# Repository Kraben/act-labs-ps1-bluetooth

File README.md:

# ACT Labs REX PS1 Replacement PCB

> Placa de repuesto open-source para el **ACT Labs REX Arcade Stick de PS1**.

```text
Status: Hardware V2 / KiCad actualizado
Firmware publico: PS1 Digital v1.1 OK
Firmware de apoyo: Hybrid AUTO PS1 / PS2 / BLE
BLE: operativo
Fabricacion: Gerbers pendientes de actualizar
Edicion: KiCad completo actualizado
```

## Project Dashboard

| Area | Estado | Alcance |
|---|---|---|
| Hardware | V2 / KiCad actualizado | Publico |
| Firmware PS1 | PS1 Digital v1.1 OK | Publico |
| Firmware binary | [`ActLabs_PS1_Digital_v1.1_OK.bin`](firmware/releases/PS1_Digital/v1.1/ActLabs_PS1_Digital_v1.1_OK.bin) | Publico |
| BLE HID | Operativo | Publico |
| AutoFire | Documentado | Publico |
| KiCad editable | Actualizado en `hardware/kicad/ACT_Labs_REX/` | Publico |
| Gerbers fabricacion | Pendientes de regenerar desde la revision KiCad actual | Publico |
| PS2 / DualShock | Listo en firmware Hybrid AUTO | Build de apoyo / donativos |
| PS1/PS2/BLE Hybrid | Listo en firmware Hybrid AUTO | Build de apoyo / donativos |

## Quick Links

| Recurso | Link |
|---|---|
| Sitio web | https://kraben.github.io/act-labs-ps1-bluetooth/ |
| Descargar firmware PS1 v1.1 | [`ActLabs_PS1_Digital_v1.1_OK.bin`](firmware/releases/PS1_Digital/v1.1/ActLabs_PS1_Digital_v1.1_OK.bin) |
| Firmware notes | [`docs/firmware.md`](docs/firmware.md) |
| Firmware Hybrid AUTO | [`docs/supporter-build.md`](docs/supporter-build.md) |
| Interfaz PS1 | [`docs/interfaces/ps1.md`](docs/interfaces/ps1.md) |
| Mapeo GPIO | [`docs/mapeo-gpio.md`](docs/mapeo-gpio.md) |
| Conectores | [`docs/conectores.md`](docs/conectores.md) |
| AutoFire | [`docs/autofire.md`](docs/autofire.md) |
| BOM | [`docs/bom.md`](docs/bom.md) |
| Fabricacion | [`docs/fabricacion.md`](docs/fabricacion.md) |
| KiCad editable | [`hardware/kicad/ACT_Labs_REX/`](hardware/kicad/ACT_Labs_REX/) |
| Gerbers | [`hardware/fabrication/gerbers/ACT_Labs_REX/`](hardware/fabrication/gerbers/ACT_Labs_REX/) |

## Resumen

El objetivo de este repositorio es conservar y documentar una alternativa de reemplazo para el control ACT Labs REX, ya que la pieza original ya no se fabrica ni se consigue facilmente.

El sistema usa un ESP32 DevKit V1 como controlador principal para reemplazar la electronica del ACT Labs REX Arcade Stick de PS1.

## Firmware publico PS1

La version publica actual del firmware es:

```text
ActLabs_PS1_Digital_v1.1_OK.bin
```

| Campo | Valor |
|---|---|
| Version | PS1 Digital v1.1 |
| Estado | OK |
| Target | ACT Labs REX PS1 Replacement PCB |
| Hardware | V2 / KiCad actualizado |
| Ruta | [`firmware/releases/PS1_Digital/v1.1/`](firmware/releases/PS1_Digital/v1.1/) |
| Archivo | [`ActLabs_PS1_Digital_v1.1_OK.bin`](firmware/releases/PS1_Digital/v1.1/ActLabs_PS1_Digital_v1.1_OK.bin) |
| SHA256 | `0a8994050381326bf345bf8123c105abefadabf30187247be9129a8c7f34b15c` |
| MD5 | `f61375d0dea1b9e42a6903105f5fba79` |

## Firmware Hybrid AUTO de apoyo

El firmware Hybrid AUTO es una build avanzada para ESP32 pensada como opcion de apoyo/donativos al proyecto.

| Funcion | Estado |
|---|---|
| PS1 cableado | Listo |
| PS2 / DualShock | Listo |
| Bluetooth BLE HID | Listo |
| Deteccion automatica PS1 / PS2 / BLE | Listo |

La documentacion publica se mantiene en [`docs/supporter-build.md`](docs/supporter-build.md). El codigo fuente completo del firmware Hybrid AUTO no se publica en este repositorio publico.

## Modos documentados

| Modo | Descripcion | Estado |
|---|---|---|
| PS1 cableado | ESP32 emula un control digital PS1 usando DATA, CMD, ATT, CLK y ACK. | Publico |
| Bluetooth HID | ESP32 funciona como gamepad BLE cuando se usa con bateria. | Publico |
| AutoFire | Placa secundaria con switches SPDT para activar turbo por boton. | Publico |
| Firmware Hybrid AUTO | PS1 / PS2 / BLE con deteccion automatica. | Build de apoyo / donativos |

## Estructura limpia

```text
.
├── docs/
│   ├── firmware.md
│   ├── supporter-build.md
│   ├── mapeo-gpio.md
│   ├── conectores.md
│   ├── autofire.md
│   └── interfaces/ps1.md
├── hardware/
│   ├── fabrication/
│   │   └── gerbers/
│   │       └── ACT_Labs_REX/
│   ├── kicad/
│   │   └── ACT_Labs_REX/
│   ├── pdf/
│   └── images/
├── data/
└── firmware/
    ├── ACT_Labs_Controller/
    └── releases/
        └── PS1_Digital/
            └── v1.1/
```

## Para fabricar vs para editar

| Uso | Carpeta | Contenido |
|---|---|---|
| Editar proyecto | [`hardware/kicad/ACT_Labs_REX/`](hardware/kicad/ACT_Labs_REX/) | Proyecto KiCad completo actualizado |
| Fabricar PCB | [`hardware/fabrication/gerbers/ACT_Labs_REX/`](hardware/fabrication/gerbers/ACT_Labs_REX/) | Gerbers pendientes de regenerar desde la revision KiCad actual |
| Firmware publico | [`firmware/releases/PS1_Digital/v1.1/`](firmware/releases/PS1_Digital/v1.1/) | Binario PS1 Digital v1.1 |
| Revisar PDFs | [`hardware/pdf/`](hardware/pdf/) | Esquematicos y PCB en PDF |
| Revisar datos | [`data/`](data/) | Mapeos, CSV y hojas de apoyo |

## Archivos de fabricacion actuales

> Nota: los Gerbers existentes pueden no corresponder todavia a la revision KiCad mas reciente. Regenerar y validar antes de fabricar.

| Archivo | Proposito |
|---|---|
| `ACT_Labs_REX-F_Cu.gbr` | Cobre superior |
| `ACT_Labs_REX-B_Cu.gbr` | Cobre inferior |
| `ACT_Labs_REX-F_Mask.gbr` | Mascara superior |
| `ACT_Labs_REX-B_Mask.gbr` | Mascara inferior |
| `ACT_Labs_REX-F_Silkscreen.gbr` | Serigrafia superior |
| `ACT_Labs_REX-B_Silkscreen.gbr` | Serigrafia inferior |
| `ACT_Labs_REX-Edge_Cuts.gbr` | Contorno de PCB |
| `ACT_Labs_REX-PTH.drl` | Taladros metalizados |
| `ACT_Labs_REX-NPTH.drl` | Taladros no metalizados |
| `ACT_Labs_REX-job.gbrjob` | Job file de fabricacion |

## Referencias de hardware

| Archivo | Descripcion |
|---|---|
| [`hardware/pdf/ACT_Labs_REX.pdf`](hardware/pdf/ACT_Labs_REX.pdf) | Esquematico principal |
| [`hardware/pdf/ArcLabsPCB.pdf`](hardware/pdf/ArcLabsPCB.pdf) | PCB principal |
| [`hardware/pdf/AutoFire.pdf`](hardware/pdf/AutoFire.pdf) | Esquematico AutoFire |
| [`hardware/pdf/AutoFirePCB.pdf`](hardware/pdf/AutoFirePCB.pdf) | PCB AutoFire |
| [`hardware/fabrication/`](hardware/fabrication/) | BOM/POS de fabricacion |

## Pines principales V2

| Signal | GPIO |
|---|---:|
| DATA | 19 |
| CMD | 23 |
| ATT | 5 |
| CLK | 18 |
| ACK | 4 |
| START | 2 |
| SELECT | 16 |
| AF_MODE | 15 |

## Apoyo / donativos

GitHub Pages puede funcionar como landing page del proyecto y enlazar a una plataforma externa para apoyo/donativos.

Opciones recomendadas:

| Opcion | Uso recomendado |
|---|---|
| GitHub Pages + PayPal/Mercado Pago | Catalogo simple y contacto directo |
| GitHub Pages + Gumroad/Payhip/Ko-fi | Entrega de builds de apoyo, firmware o archivos digitales |
| GitHub Pages + Stripe Payment Links | Botones de pago profesionales sin backend propio |
| GitHub Sponsors | Apoyo/donaciones recurrentes |

El repositorio publico mantiene hardware, documentacion y firmware PS1 disponible. La build Hybrid AUTO se maneja como opcion avanzada de apoyo para sostener el desarrollo.

## Proximos pasos

- [ ] Regenerar Gerbers desde la revision KiCad actual.
- [ ] Validar Gerbers nuevos contra visualizador antes de mandar a fabricar.
- [ ] Validar continuidad START/SELECT contra GND en PCB actualizada.
- [ ] Validar continuidad entre PCB principal, placa AutoFire y conectores JP.
- [ ] Revisar la ruta de alimentacion `BATT_FROM_TP`, TP4056, LD1117-3.3 y diodos SS14.
- [ ] Validar el firmware PS1 actualizado contra hardware fisico.
- [ ] Confirmar pull-ups reales contra la PCB antes de fabricar.
- [ ] Preparar binario, checksums y guia de flasheo para la build Hybrid AUTO de apoyo.

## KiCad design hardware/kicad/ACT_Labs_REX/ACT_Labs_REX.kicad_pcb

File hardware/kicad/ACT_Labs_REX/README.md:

# ACT Labs REX KiCad Sources

Fuentes editables de KiCad para **ACT Labs REX PCB V2.2**.

## Uso

Esta carpeta es para editar el proyecto en KiCad.

Para fabricar usar los Gerbers exportados en:

```text
hardware/fabrication/gerbers/ACT_Labs_REX/
```

## Archivos principales

| Archivo | Proposito |
|---|---|
| ACT_Labs_REX.kicad_pro | Proyecto KiCad |
| ACT_Labs_REX.kicad_sch | Esquematico principal |
| ACT_Labs_REX.kicad_pcb | PCB principal |
| Placa_2.kicad_sch | Esquematico de placa secundaria / AutoFire |

## Reglas

- Mantener aqui solo fuentes editables de KiCad.
- No mezclar Gerbers ni salidas de fabricacion en esta carpeta.
- No subir backups, autosaves ni archivos temporales.
- Exportar salidas de fabricacion hacia `hardware/fabrication/gerbers/ACT_Labs_REX/`.

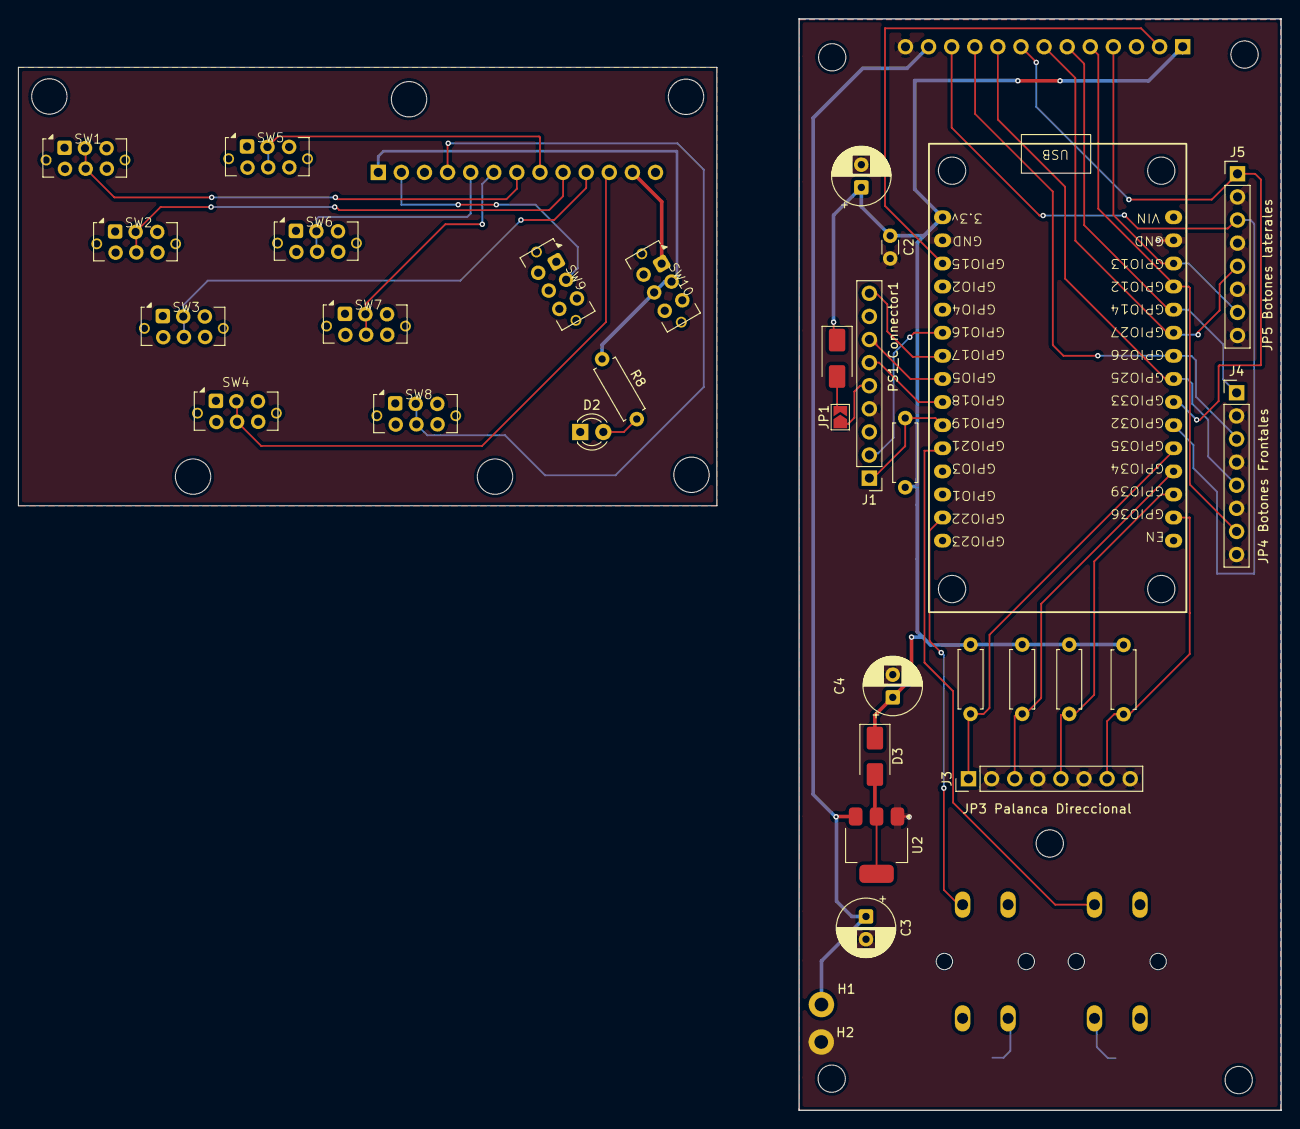
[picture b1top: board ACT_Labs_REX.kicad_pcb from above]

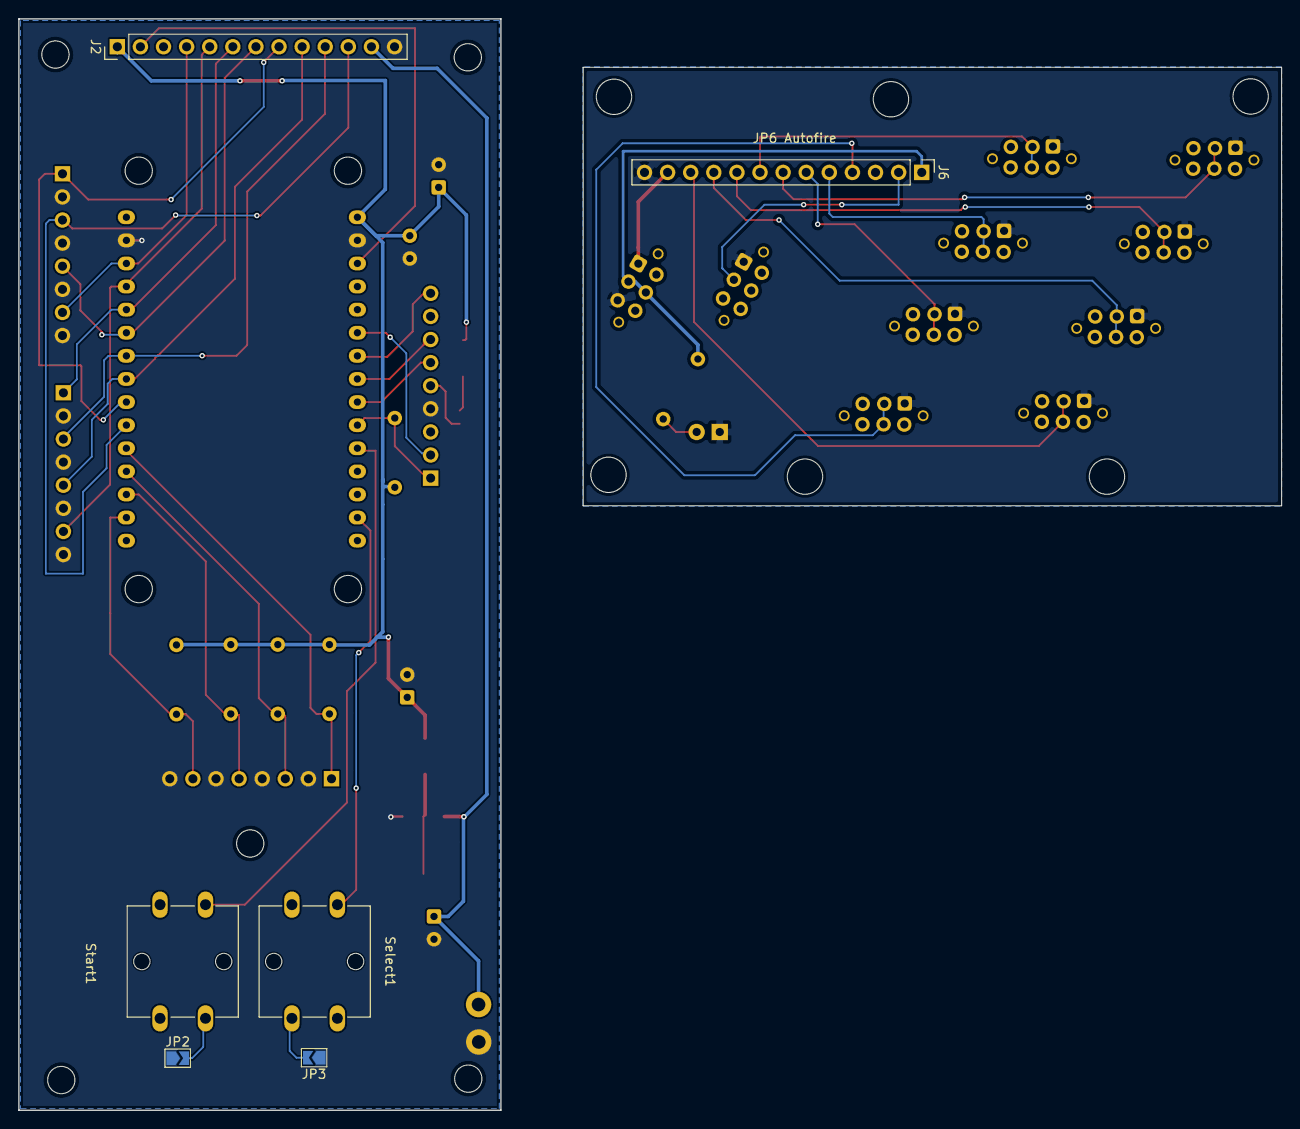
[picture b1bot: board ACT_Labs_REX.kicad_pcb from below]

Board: 2 copper layers, 138.8 x 120.0 mm, 38 parts (6 on the bottom side), 35 nets.

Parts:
C1: 220µF; CP_Radial_D6.3mm_P2.50mm
C2: 100nF; C_Disc_D3.0mm_W1.6mm_P2.50mm
C3, C4: 10µF; CP_Radial_D6.3mm_P2.50mm
D1, D3: SS14; D_SMA
D2: LED; LED_D3.0mm
H1, H2: TP4056; MountingHole_2.5mm_Pad
J1: PS1_Connector1; PinHeader_1x09_P2.54mm_Vertical
J2: JP1 Autofire; PinHeader_1x13_P2.54mm_Vertical
J3: JP3 Palanca Direccional; PinHeader_1x08_P2.54mm_Vertical
J4: JP4 Botones Frontales; PinHeader_1x08_P2.54mm_Vertical
J5: JP5 Botones laterales; PinHeader_1x08_P2.54mm_Vertical
J6: JP6 Autofire; PinHeader_1x13_P2.54mm_Vertical
JP1, JP2, JP3: SolderJumper_2_Open; SolderJumper-2_P1.3mm_Open_TrianglePad1.0x1.5mm
R1, R2, R3, R4, R5: 10kΩ; R_Axial_DIN0207_L6.3mm_D2.5mm_P7.62mm_Horizontal
R8: 220Ω; R_Axial_DIN0207_L6.3mm_D2.5mm_P7.62mm_Horizontal
SW1, SW2, SW3, SW4, SW5, SW6, SW7, SW8, SW9, SW10: SW_SPDT; Untitled_1
Select1: SW_Omron_B3FS; SW_SPST_Omron_B3F-50xx
Start1: SW_Omron_B3FS; SW_SPST_Omron_B3F-50xx
U1: ESP32_30pin
U2: LD1117S33TR_SOT223; SOT-223-3_TabPin2

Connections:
//AF_CIRCULO: J2.10, J4.3, U1.7 (GPIO26)
//AF_CRUZ: J2.9, J4.5, U1.8 (GPIO25)
//AF_CUADRADO: J2.5, J4.7, U1.4 (GPIO12)
//AF_L1: J2.7, J5.5, U1.6 (GPIO27)
//AF_L2: J2.11, J5.3, U1.10 (GPIO32)
//AF_MODE: J2.2, U1.18 (GPIO15)
//AF_R1: J2.8, J5.1, U1.9 (GPIO33)
//AF_R2: J2.4, J5.7, U1.3 (GPIO13)
//AF_TRIANGULO: J2.6, J4.1, U1.5 (GPIO14)
//AutoFire/AF_CIRCULO: J6.10, SW3.2 (B), SW3.5
//AutoFire/AF_CRUZ: J6.9, SW2.2 (B), SW2.5
//AutoFire/AF_CUADRADO: J6.5, SW6.2 (B), SW6.5
//AutoFire/AF_L1: J6.7, SW1.2 (B), SW1.5
//AutoFire/AF_L2: J6.11, SW4.2 (B), SW4.5
//AutoFire/AF_MODE: J6.2, SW9.2 (B)
//AutoFire/AF_R1: J6.8, SW5.2 (B), SW5.5
//AutoFire/AF_R2: J6.4, SW8.2 (B), SW8.5
//AutoFire/AF_TRIANGULO: J6.6, SW7.2 (B), SW7.5
//AutoFire/GND: D2.1 (K), J6.13, SW1.1 (A), SW2.1 (A), SW3.1 (A), SW4.1 (A), SW5.1 (A), SW6.1 (A), SW7.1 (A), SW8.1 (A), SW9.1 (A), SW10.3 (C)
//AutoFire/LED: D2.2 (A), R8.2
//GND: C1.2, C2.2, C3.2, C4.2, H2.1 (1_1), J1.4, J2.13, J3.2, J3.4, J3.6, J3.8, J4.2, J4.4, J4.6, J4.8, J5.2, J5.4, J5.6, J5.8, JP2.1 (A), JP3.1 (A), U1.2 (GND), U1.17 (GND), U2.1 (GND)
//JP3_ABAJO: J3.1, R4.2, U1.11 (GPIO35)
//JP3_ARRIBA: J3.7, R2.2, U1.14 (GPIO36)
//JP3_DERECHA: J3.5, R5.2, U1.13 (GPIO39)
//JP3_IZQUIERDA: J3.3, R3.2, U1.12 (GPIO34)
//PS1_ACK: J1.9, U1.22 (GPIO17)
//PS1_ATT: J1.6, U1.24 (GPIO18)
//PS1_CLK: J1.7, U1.23 (GPIO5)
//PS1_CMD: J1.2, U1.21 (GPIO16)
//PS1_DATA: J1.1, R1.2, U1.25 (GPIO19)
//SELECT: JP3.2 (B), Select1.3, Select1.4, U1.29 (GPIO22)
//START: JP2.2 (B), Start1.1 (1_1), Start1.4, U1.26 (GPIO21)
BATT_FROM_TP: C3.1, H1.1 (1_1), J2.12, J6.12, SW10.1 (A), U2.3 (VI)
PS1_PIN5: D1.2 (A), J1.5, JP1.1 (A), JP1.2 (B)
VCC_3V3: C1.1, C2.1, C4.1, D1.1 (K), D3.1 (K), D3.2 (A), J2.1, J6.1, R1.1, R2.1, R3.1, R4.1, R5.1, R8.1, SW10.2 (B), SW10.5, U1.16 (3.3v), U2.2 (VO)

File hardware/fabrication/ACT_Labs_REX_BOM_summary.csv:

Reference,Value,Quantity
C1,220uF,1
C2,100nF,1
C3,10uF,1
C4,10uF,1
D1,SS14,1
D2,LED,1
D3,SS14,1
J1,PS1_Connector1,1
J2,JP1_Autofire,1
J3,JP3_Palanca_Direccional,1
J4,JP4_Botones_Frontales,1
J5,JP5_Botones_laterales,1
J6,JP6_Autofire,1
R1,10k,1
R2,10k,1
R3,10k,1
R4,10k,1
R5,10k,1
R6,4.7k,1
R7,4.7k,1
R8,220R,1
Select1,SW_Omron_B3FS,1
Start1,SW_Omron_B3FS,1
SW1,SW_SPDT,1
SW2,SW_SPDT,1
SW3,SW_SPDT,1
SW4,SW_SPDT,1
SW5,SW_SPDT,1
SW6,SW_SPDT,1
SW7,SW_SPDT,1
SW8,SW_SPDT,1
SW9,SW_SPDT,1
SW10,SW_SPDT,1
U1,ESP32_30pin,1
U2,LD1117S33TR_SOT223,1

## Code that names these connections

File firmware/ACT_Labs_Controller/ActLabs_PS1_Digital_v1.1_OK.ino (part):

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  - Turbo opcional.

  Pines protocolo:
    DATA = GPIO19  ESP32 -> PS1
    CMD  = GPIO23  PS1 -> ESP32
    ATT  = GPIO5   PS1 -> ESP32
    CLK  = GPIO18  PS1 -> ESP32
    ACK  = GPIO4   ESP32 -> PS1

  Pull-ups recomendados:
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// PINES PS1
// =====================================================

#define PS1_DATA  19
#define PS1_CMD   23
#define PS1_ATT   5
#define PS1_CLK   18
#define PS1_ACK   4

// =====================================================
// BOTONES SEGUN ESQUEMATICO ACTLABS
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
#define PIN_START      21
#define PIN_SELECT     22
#define PIN_AF_MODE    15

// =====================================================
// MAPA PS1 DIGITAL
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volatile uint32_t ps1_att_count = 0;
volatile uint32_t ps1_clk_count = 0;

static const uint32_t DATA_MASK = (1UL << PS1_DATA);
static const uint32_t ACK_MASK  = (1UL << PS1_ACK);

// =====================================================
// LINEAS OPEN-DRAIN POR REGISTRO
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
  pinMode(PIN_START, INPUT_PULLUP);
  pinMode(PIN_SELECT, INPUT_PULLUP);
  pinMode(PIN_AF_MODE, INPUT_PULLUP);

  // Palanca: GPIO34/35/36/39 con resistencias fisicas externas de 10k.
  pinMode(PIN_ARRIBA, INPUT);
  pinMode(PIN_ABAJO, INPUT);
  pinMode(PIN_IZQUIERDA, INPUT);
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// =====================================================

void setupPs1Pins() {
  pinMode(PS1_CMD, INPUT);
  pinMode(PS1_ATT, INPUT_PULLUP);
  pinMode(PS1_CLK, INPUT_PULLUP);

  // DATA y ACK quedan high-Z.
  dataHighZ();
  ackHighZ();

  attachInterrupt(digitalPinToInterrupt(PS1_ATT), attISR, CHANGE);

  // PS1 funcional: RISING.
  attachInterrupt(digitalPinToInterrupt(PS1_CLK), clkISR, RISING);
}

// =====================================================
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
  Serial.println();
  Serial.println("Mapeo:");
  Serial.println("GPIO25 = X / CRUZ");
  Serial.println("GPIO26 = CIRCLE / CIRCULO");
  Serial.println("GPIO12 = SQUARE / CUADRADO");
  Serial.println("GPIO14 = TRIANGLE / TRIANGULO");
  Serial.println("GPIO27 = L1");
  Serial.println("GPIO33 = R1");
  Serial.println("GPIO32 = L2");
  Serial.println("GPIO13 = R2");
  Serial.println("GPIO21 = START");
  Serial.println("GPIO22 = SELECT");
  Serial.println("GPIO34 = UP");
  Serial.println("GPIO36 = DOWN");
  Serial.println("GPIO39 = LEFT");
  Serial.println("GPIO35 = RIGHT");
  Serial.println();

  Serial.println("Esperado:");
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
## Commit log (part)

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2026-05-08 Initial ACT Labs PS1 Bluetooth project
2026-06-24 V2 PCB checkpoint: LD1117, TP4056, D1, DATA ACK pullups
2026-06-24 Update V2 documentation exports, BOM and fabrication files
2026-06-24 Remove duplicate position exports
2026-06-24 Remove legacy schematic PDF and keep V2 as official release
2026-06-24 docs: actualiza arquitectura V2
2026-06-24 docs: actualiza BOM V2
2026-06-24 docs: actualiza conectores V2
2026-06-24 docs: actualiza firmware V2
2026-06-24 docs: actualiza mapeo GPIO V2
2026-06-24 docs: sincroniza README con hardware V2 y archivos de fabricacion
2026-06-24 docs: documenta arquitectura V2 completa
2026-06-24 docs: actualiza BOM desde exportaciones KiCad V2
2026-06-24 docs: amplía mapeo GPIO V2 para firmware
2026-06-24 docs: actualiza conectores V2 con TP4056 y J1-J6
2026-06-24 docs: actualiza firmware con pines V2 y plan PS1
2026-06-24 docs: actualiza resumen de hardware y fabricacion
2026-06-24 docs: agrega guia de fabricacion V2
2026-06-24 docs: agrega registro de revision V2
2026-06-24 docs: agrega inventario de fuentes KiCad V2
2026-06-24 hardware: agrega resumen BOM placa principal V2
2026-06-24 hardware: agrega resumen POS placa principal V2
2026-06-24 hardware: agrega resumen BOM AutoFire V2
2026-06-24 hardware: agrega resumen POS AutoFire V2
2026-06-24 docs: ajusta referencias a archivos de fabricacion cargados
2026-06-24 docs: ajusta hardware README a resumenes de fabricacion
2026-06-24 docs: corrige START y SELECT segun mapeo consolidado
2026-06-24 docs: sincroniza mapeo GPIO con Rev 1.4
2026-06-24 docs: sincroniza firmware con resumen y pines Rev 1.4
2026-06-24 docs: consolida conectores y corrige tabla JP1
2026-06-24 docs: corrige revision V2 con mapeo Rev 1.4
2026-06-24 docs: actualiza inventario de fuentes y hashes Rev 1.4
2026-06-26 docs: agrega arquitectura de interfaces
2026-06-26 docs: agrega interfaz PS1
2026-06-26 docs: agrega interfaz SNES futura
2026-06-26 docs: agrega interfaz Genesis futura
2026-06-26 docs: agrega interfaz N64 futura
2026-06-26 docs: agrega interfaz GameCube futura
2026-06-26 docs: enlaza carpeta de interfaces en README
2026-06-26 docs: agrega referencia ESP32 pinout y notas GPIO
2026-06-27 chore: organiza fuentes KiCad y datos del proyecto
2026-06-28 Add KrabenStick landing page
2026-06-28 Add KrabenStick site styles
2026-06-28 Rebrand project as KrabenStick ESP32
2026-06-28 Add KrabenStick SVG logo asset
2026-06-28 Use KrabenStick logo on landing page
2026-06-28 Style KrabenStick logo integration
2026-06-28 Create logo
2026-06-28 docs: elimina interfaz futura SNES
2026-06-28 docs: elimina interfaz futura Genesis
2026-06-28 docs: elimina interfaz futura N64
2026-06-28 docs: remove future GameCube interface
2026-06-28 docs: elimina arquitectura de interfaces futuras
2026-06-28 docs: enfoca README en reemplazo ACT Labs REX PS1
2026-06-28 docs: ajusta sitio a placa de repuesto ACT Labs REX
2026-06-28 docs: corrige enfoque ACT Labs REX y ruta del logo
2026-06-28 docs: aclara que PS2 aun no esta implementado
2026-06-28 docs: marca compatibilidad PS2 como no implementada
2026-06-28 Add PayPal donation button
2026-06-28 Style PayPal donation button
2026-06-29 Create krabenstick-logo
2026-06-29 Rename krabenstick-logo.png to krabenstick-logo1.png
2026-06-29 Rename krabenstick-logo1.png to krabenstick-logo.png
